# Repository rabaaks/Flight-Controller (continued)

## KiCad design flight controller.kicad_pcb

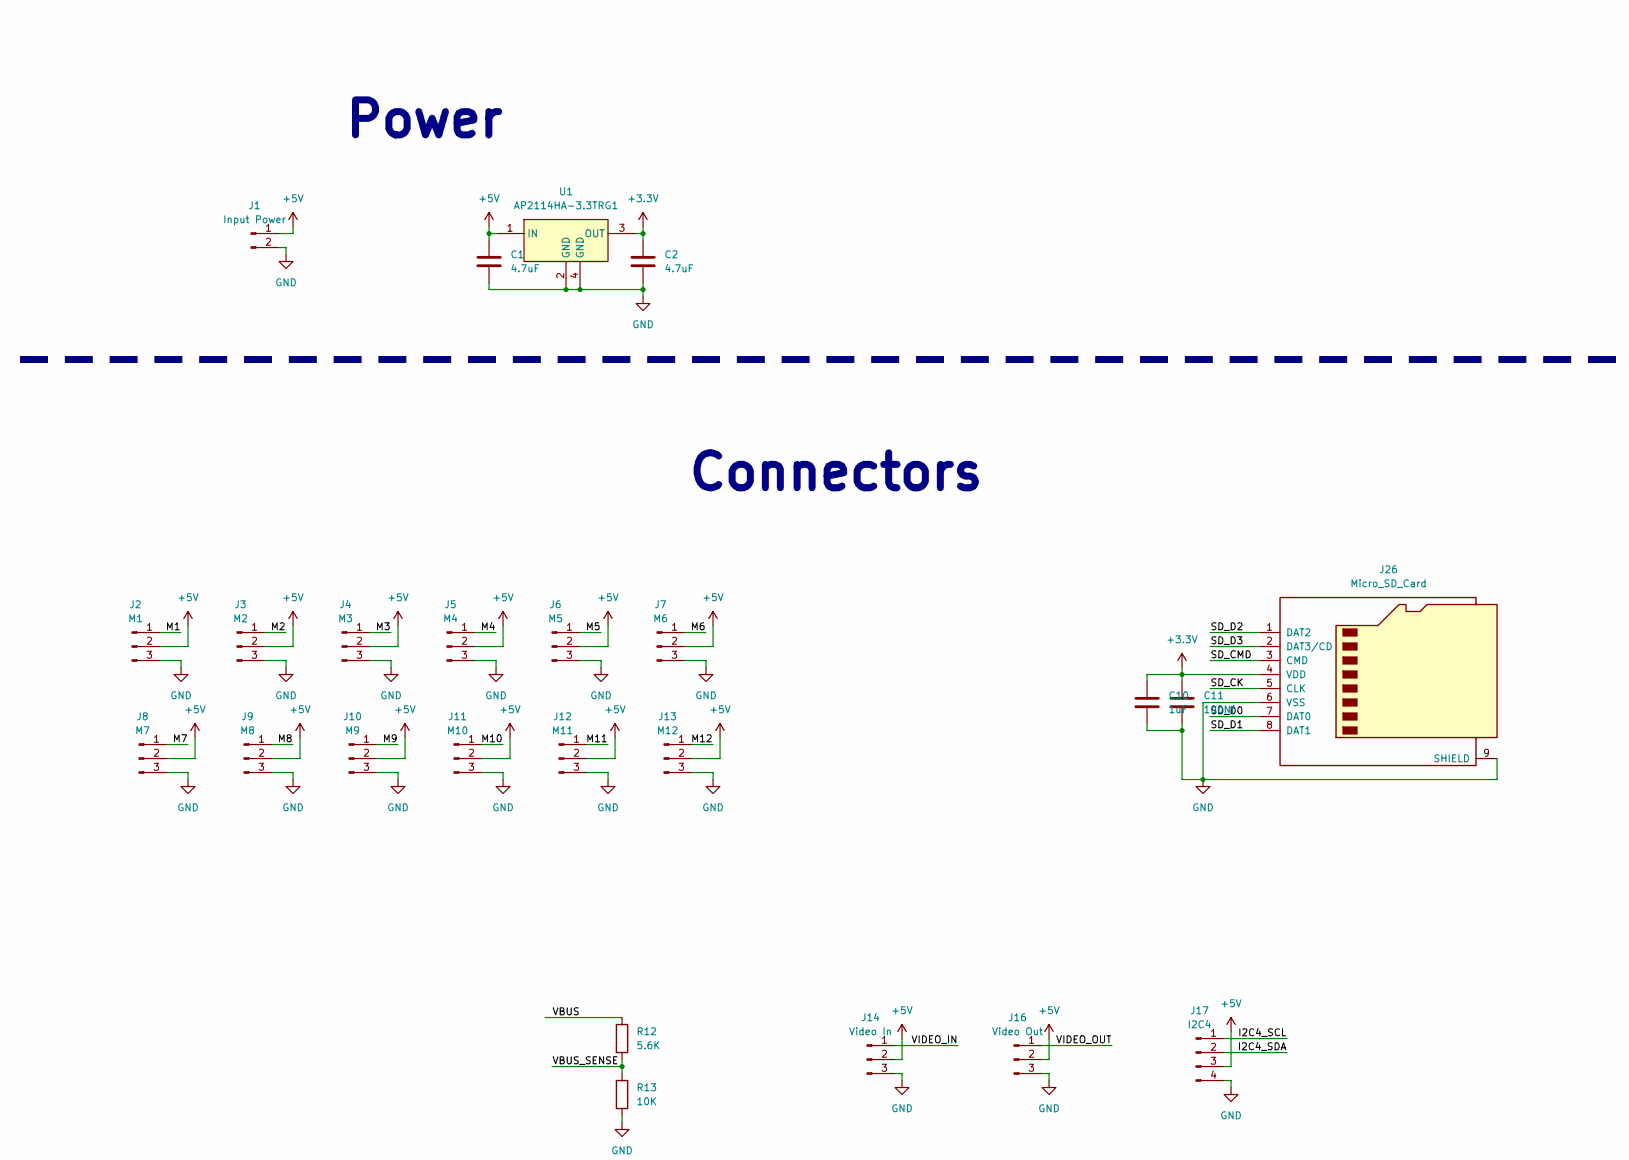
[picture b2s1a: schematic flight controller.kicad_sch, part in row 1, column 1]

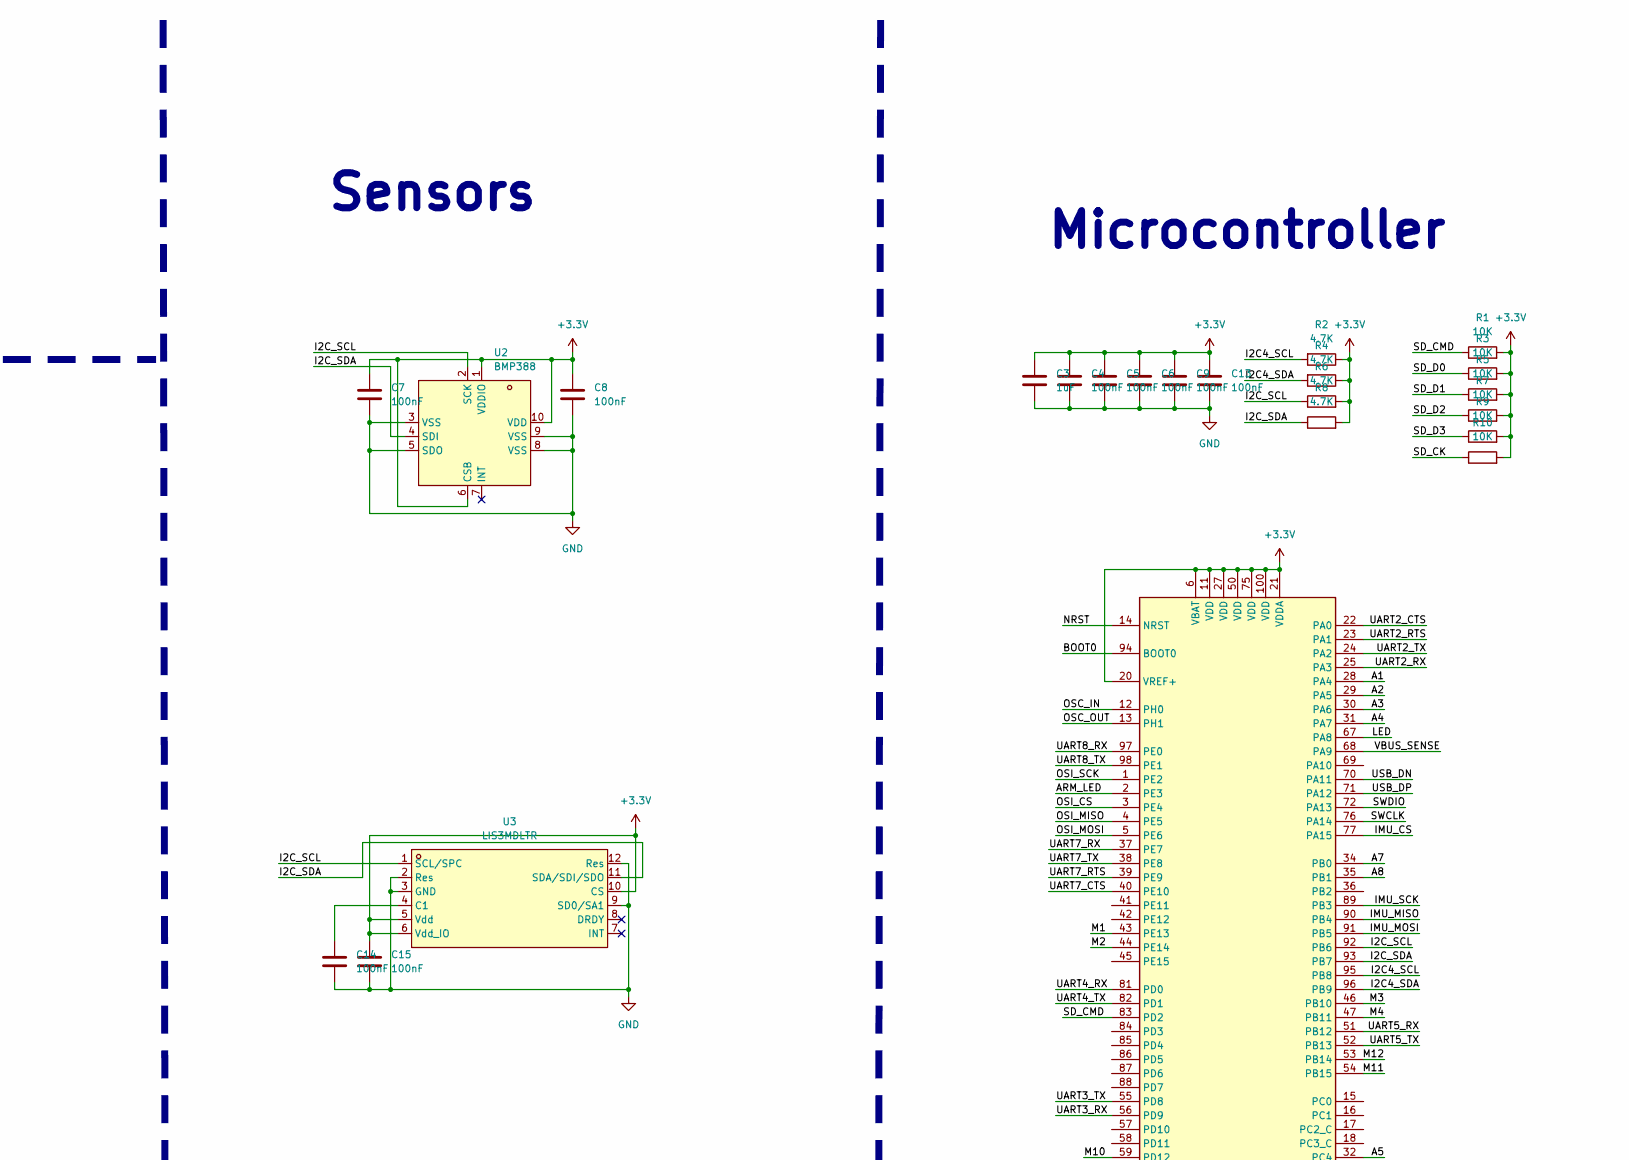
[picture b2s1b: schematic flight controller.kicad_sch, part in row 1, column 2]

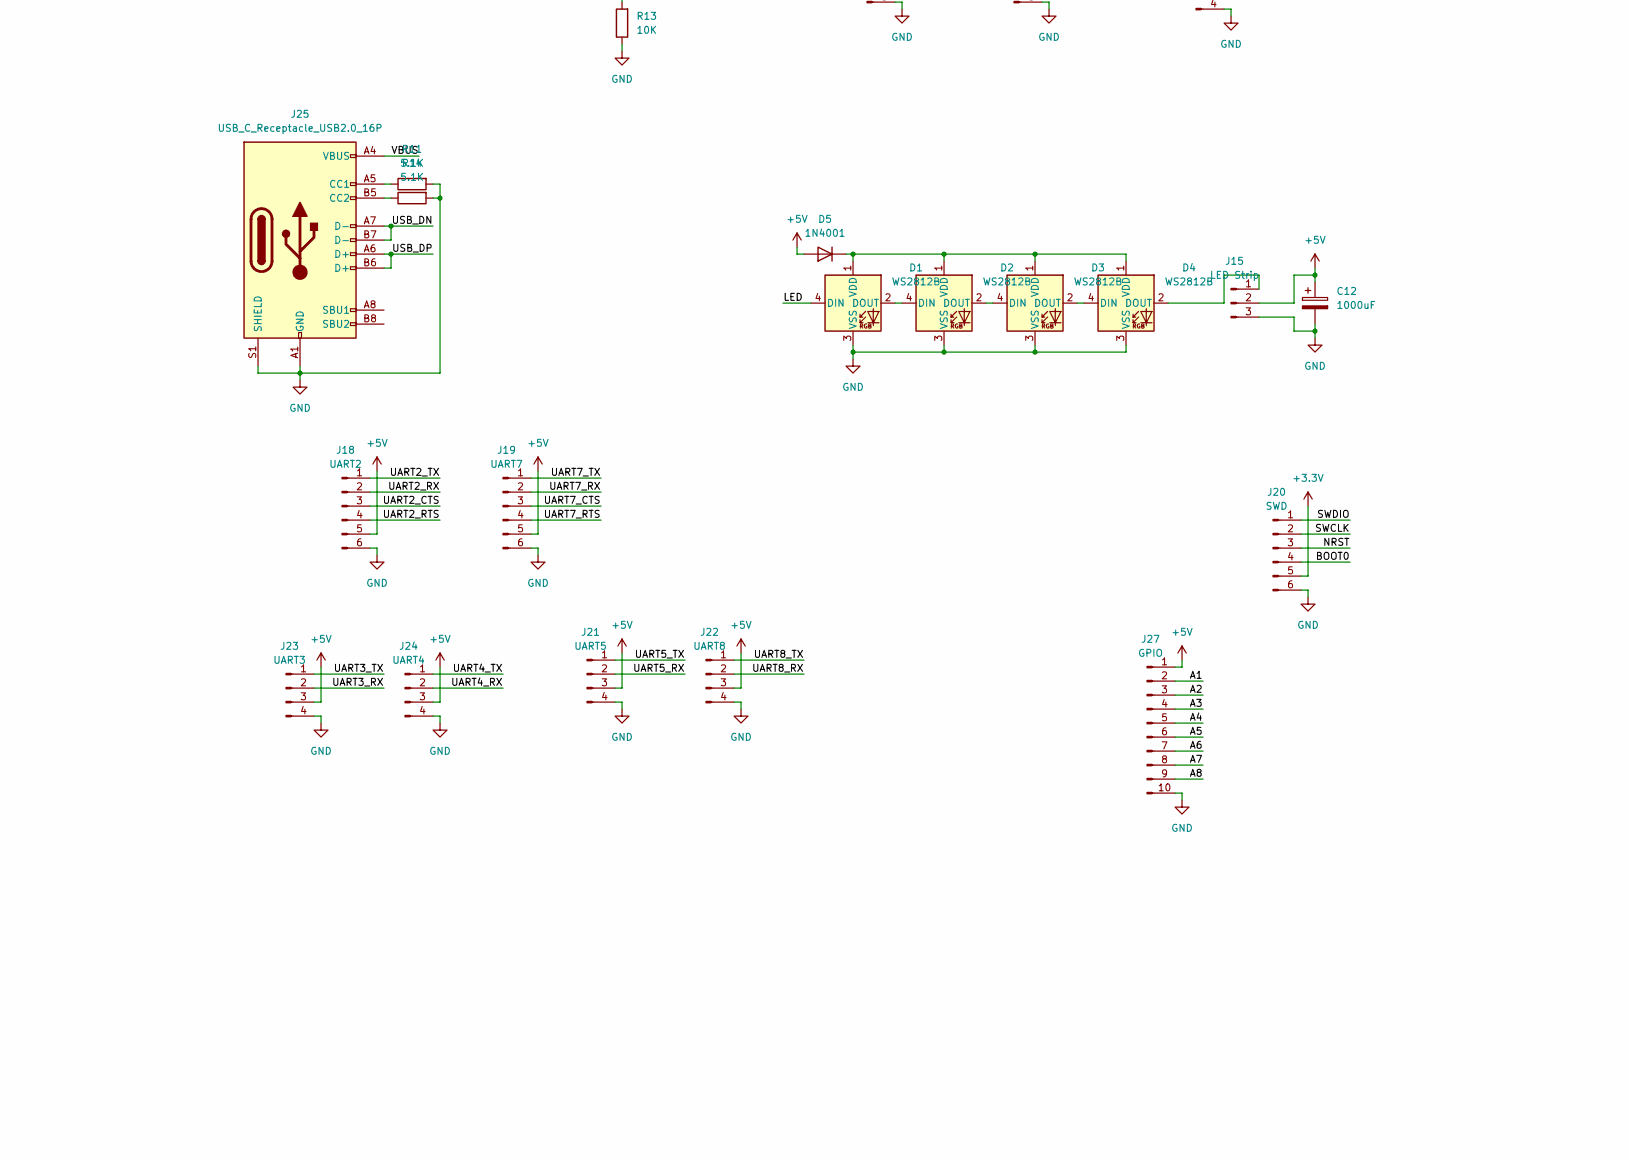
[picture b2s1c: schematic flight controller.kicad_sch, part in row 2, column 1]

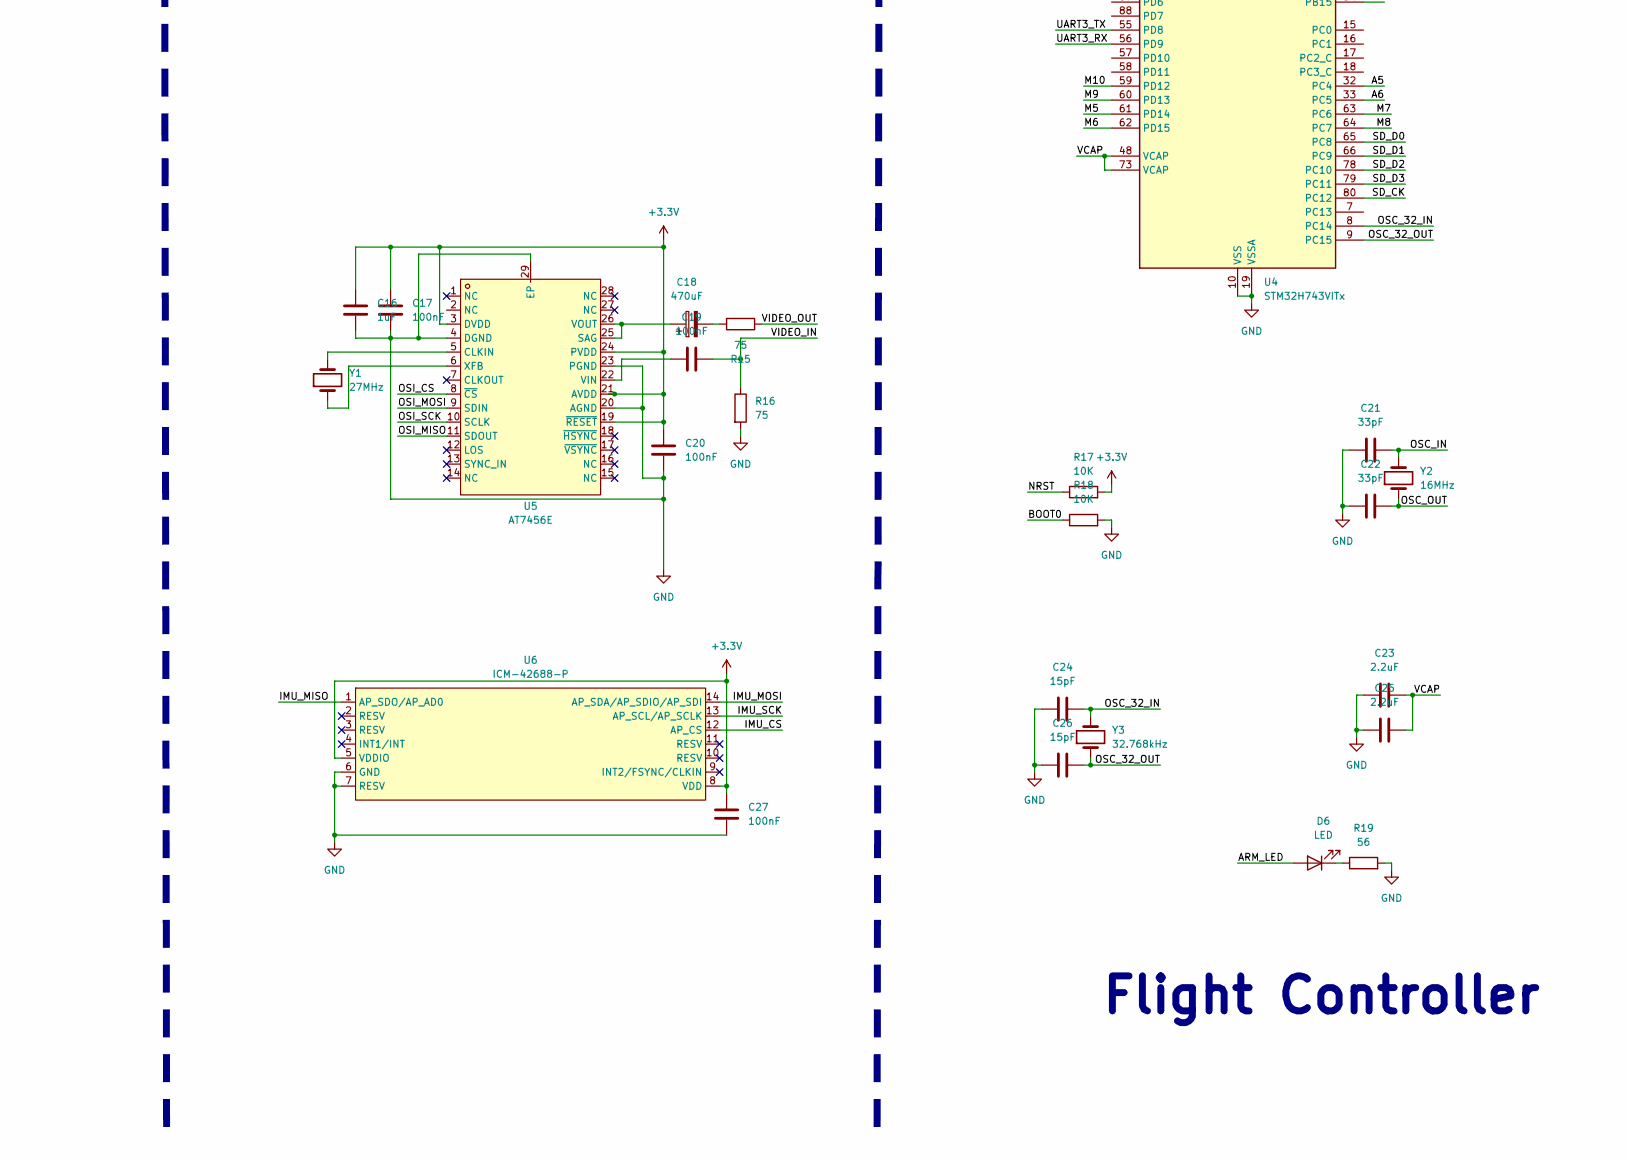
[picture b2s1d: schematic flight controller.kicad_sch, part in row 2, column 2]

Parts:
C1, C2: 4.7uF; C_0805_2012Metric
C3, C10, C16: 1uF; C_0805_2012Metric
C4, C5, C6, C7, C8, C9, C13, C14, C15, C17, C19, C20, C27: 100nF; C_0805_2012Metric
C11: 100Nf; C_0805_2012Metric
C12: 1000uF; CP_Radial_D8.0mm_P3.50mm
C18: 470uF; CP_Radial_D8.0mm_P3.50mm
C21, C22: 33pF; C_0805_2012Metric
C23, C25: 2.2uF; C_0805_2012Metric
C24, C26: 15pF; C_0805_2012Metric
D1, D2, D3, D4: WS2812B; LED_WS2812B_PLCC4_5.0x5.0mm_P3.2mm
D5: 1N4001; D_DO-41_SOD81_P7.62mm_Horizontal
D6: LED; LED_0805_2012Metric
J1: Input Power; AMASS_XT30PW-M_1x02_P2.50mm_Horizontal
J2: M1; JST_XH_B3B-XH-A_1x03_P2.50mm_Vertical
J3: M2; JST_XH_B3B-XH-A_1x03_P2.50mm_Vertical
J4: M3; JST_XH_B3B-XH-A_1x03_P2.50mm_Vertical
J5: M4; JST_XH_B3B-XH-A_1x03_P2.50mm_Vertical
J6: M5; JST_XH_B3B-XH-A_1x03_P2.50mm_Vertical
J7: M6; JST_XH_B3B-XH-A_1x03_P2.50mm_Vertical
J8: M7; JST_XH_B3B-XH-A_1x03_P2.50mm_Vertical
J9: M8; JST_XH_B3B-XH-A_1x03_P2.50mm_Vertical
J10: M9; JST_XH_B3B-XH-A_1x03_P2.50mm_Vertical
J11: M10; JST_XH_B3B-XH-A_1x03_P2.50mm_Vertical
J12: M11; JST_XH_B3B-XH-A_1x03_P2.50mm_Vertical
J13: M12; JST_XH_B3B-XH-A_1x03_P2.50mm_Vertical
J14: Video In; JST_XH_B3B-XH-A_1x03_P2.50mm_Vertical
J15: LED Strip; JST_XH_B3B-XH-A_1x03_P2.50mm_Vertical
J16: Video Out; JST_XH_B3B-XH-A_1x03_P2.50mm_Vertical
J17: I2C4; JST_XH_B4B-XH-A_1x04_P2.50mm_Vertical
J18: UART2; JST_XH_B6B-XH-A_1x06_P2.50mm_Vertical
J19: UART7; JST_XH_B6B-XH-A_1x06_P2.50mm_Vertical
J20: SWD; JST_XH_B6B-XH-A_1x06_P2.50mm_Vertical
J21: UART5; JST_XH_B4B-XH-A_1x04_P2.50mm_Vertical
J22: UART8; JST_XH_B4B-XH-A_1x04_P2.50mm_Vertical
J23: UART3; JST_XH_B4B-XH-A_1x04_P2.50mm_Vertical
J24: UART4; JST_XH_B4B-XH-A_1x04_P2.50mm_Vertical
J25: USB_C_Receptacle_USB2.0_16P; USB_C_Receptacle_HCTL_HC-TYPE-C-16P-01A
J26: Micro_SD_Card; TF-SMD_TF-PUSH
J27: GPIO; JST_XH_B10B-XH-A_1x10_P2.50mm_Vertical
R1, R3, R5, R7, R9, R10, R13, R17, R18: 10K; R_0805_2012Metric
R2, R4, R6, R8: 4.7K; R_0805_2012Metric
R11, R14: 5.1K; R_0805_2012Metric
R12: 5.6K; R_0805_2012Metric
R15, R16: 75; R_0805_2012Metric
R19: 56; R_0805_2012Metric
U1: AP2114HA-3.3TRG1; SOT-223; LCSC Part C460314
U2: BMP388; ST_HLGA-10_2x2mm_P0.5mm_LayoutBorder3x2y; LCSC Part C779278
U3: LIS3MDLTR; LGA-12_2x2mm_P0.5mm; LCSC Part C478483
U4: STM32H743VITx; LQFP-100_14x14mm_P0.5mm
U5: AT7456E; TSSOP-28-1EP_4.4x9.7mm_P0.65mm_EP2.85x6.7mm; LCSC Part C82351
U6: ICM-42688-P; LGA-14_3x2.5mm_P0.5mm_LayoutBorder3x4y; LCSC Part C1850418
Y1: 27MHz; Crystal_HC49-U_Vertical
Y2: 16MHz; Crystal_HC49-U_Vertical
Y3: 32.768kHz; Crystal_DS26_D2.0mm_L6.0mm_Horizontal

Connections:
+3.3V: C2.1, C3.2, C4.1, C5.2, C6.1, C7.1, C8.2, C9.2, C10.2, C11.2, C13.2, C15.1, C16.1, C17.1, C20.1, C27.2, J20.5, J26.4 (VDD), R1.2, R2.1, R3.2, R4.1, R5.2, R6.2, R7.2, R8.2, R9.2, R10.2, R17.2, U1.3 (OUT), U2.1 (VDDIO), U2.6 (CSB), U2.10 (VDD), U3.5 (Vdd), U3.6 (Vdd_IO), U3.10 (CS), U4.6 (VBAT), U4.11 (VDD), U4.20 (VREF+), U4.21 (VDDA), U4.27 (VDD), U4.50 (VDD), U4.75 (VDD), U4.100 (VDD), U5.3 (DVDD), U5.19 (~RESET), U5.21 (AVDD), U5.24 (PVDD), U6.5 (VDDIO), U6.8 (VDD)
+5V: C1.1, C12.1, D5.2 (A), J1.1, J2.2, J3.2, J4.2, J5.2, J6.2, J7.2, J8.2, J9.2, J10.2, J11.2, J12.2, J13.2, J14.2, J15.2, J16.2, J17.3, J18.5, J19.5, J21.3, J22.3, J23.3, J24.3, J27.1, U1.1 (IN)
/A1: J27.2, U4.28 (PA4)
/A2: J27.3, U4.29 (PA5)
/A3: J27.4, U4.30 (PA6)
/A4: J27.5, U4.31 (PA7)
/A5: J27.6, U4.32 (PC4)
/A6: J27.7, U4.33 (PC5)
/A7: J27.8, U4.34 (PB0)
/A8: J27.9, U4.35 (PB1)
/ARM_LED: D6.2 (A), U4.2 (PE3)
/BOOT0: J20.4, R18.1, U4.94 (BOOT0)
/I2C4_SCL: J17.1, R2.2, U4.95 (PB8)
/I2C4_SDA: J17.2, R4.2, U4.96 (PB9)
/I2C_SCL: R6.1, U2.2 (SCK), U3.1 (SCL/SPC), U4.92 (PB6)
/I2C_SDA: R8.1, U2.4 (SDI), U3.11 (SDA/SDI/SDO), U4.93 (PB7)
/IMU_CS: U4.77 (PA15), U6.12 (AP_CS)
/IMU_MISO: U4.90 (PB4), U6.1 (AP_SDO/AP_AD0)
/IMU_MOSI: U4.91 (PB5), U6.14 (AP_SDA/AP_SDIO/AP_SDI)
/IMU_SCK: U4.89 (PB3), U6.13 (AP_SCL/AP_SCLK)
/LED: D1.4 (DIN), U4.67 (PA8)
/M1: J2.1, U4.43 (PE13)
/M2: J3.1, U4.44 (PE14)
/M3: J4.1, U4.46 (PB10)
/M4: J5.1, U4.47 (PB11)
/M5: J6.1, U4.61 (PD14)
/M6: J7.1, U4.62 (PD15)
/M7: J8.1, U4.63 (PC6)
/M8: J9.1, U4.64 (PC7)
/M9: J10.1, U4.60 (PD13)
/M10: J11.1, U4.59 (PD12)
/M11: J12.1, U4.54 (PB15)
/M12: J13.1, U4.53 (PB14)
/NRST: J20.3, R17.1, U4.14 (NRST)
/OSC_32_IN: C24.1, U4.8 (PC14), Y3.2
/OSC_32_OUT: C26.2, U4.9 (PC15), Y3.1
/OSC_IN: C21.1, U4.12 (PH0), Y2.2
/OSC_OUT: C22.2, U4.13 (PH1), Y2.1
/OSI_CS: U4.3 (PE4), U5.8 (~CS)
/OSI_MISO: U4.4 (PE5), U5.11 (SDOUT)
/OSI_MOSI: U4.5 (PE6), U5.9 (SDIN)
/OSI_SCK: U4.1 (PE2), U5.10 (SCLK)
/SD_CK: J26.5 (CLK), R10.1, U4.80 (PC12)
/SD_CMD: J26.3 (CMD), R1.1, U4.83 (PD2)
/SD_D0: J26.7 (DAT0), R3.1, U4.65 (PC8)
/SD_D1: J26.8 (DAT1), R5.1, U4.66 (PC9)
/SD_D2: J26.1 (DAT2), R7.1, U4.78 (PC10)
/SD_D3: J26.2 (DAT3/CD), R9.1, U4.79 (PC11)
/SWCLK: J20.2, U4.76 (PA14)
/SWDIO: J20.1, U4.72 (PA13)
/UART2_CTS: J18.3, U4.22 (PA0)
/UART2_RTS: J18.4, U4.23 (PA1)
/UART2_RX: J18.2, U4.25 (PA3)
/UART2_TX: J18.1, U4.24 (PA2)
/UART3_RX: J23.2, U4.56 (PD9)
/UART3_TX: J23.1, U4.55 (PD8)
/UART4_RX: J24.2, U4.81 (PD0)
/UART4_TX: J24.1, U4.82 (PD1)
/UART5_RX: J21.2, U4.51 (PB12)
/UART5_TX: J21.1, U4.52 (PB13)
/UART7_CTS: J19.3, U4.40 (PE10)
/UART7_RTS: J19.4, U4.39 (PE9)
/UART7_RX: J19.2, U4.37 (PE7)
/UART7_TX: J19.1, U4.38 (PE8)
/UART8_RX: J22.2, U4.97 (PE0)
/UART8_TX: J22.1, U4.98 (PE1)
/USB_DN: J25.A7 (D-), J25.B7 (D-), U4.70 (PA11)
/USB_DP: J25.A6 (D+), J25.B6 (D+), U4.71 (PA12)
/VBUS: J25.A4 (VBUS), J25.A9 (VBUS), J25.B4 (VBUS), J25.B9 (VBUS), R12.1
/VBUS_SENSE: R12.2, R13.2, U4.68 (PA9)
/VCAP: C23.1, C25.1, U4.48 (VCAP), U4.73 (VCAP)
/VIDEO_IN: C19.2, J14.1, R16.1
/VIDEO_OUT: J16.1, R15.1
GND: C1.2, C2.2, C3.1, C4.2, C5.1, C6.2, C7.2, C8.1, C9.1, C10.1, C11.1, C12.2, C13.1, C14.2, C15.2, C16.2, C17.2, C20.2, C21.2, C22.1, C23.2, C24.2, C25.2, C26.1, C27.1, D1.3 (VSS), D2.3 (VSS), D3.3 (VSS), D4.3 (VSS), J1.2, J2.3, J3.3, J4.3, J5.3, J6.3, J7.3, J8.3, J9.3, J10.3, J11.3, J12.3, J13.3, J14.3, J15.3, J16.3, J17.4, J18.6, J19.6, J20.6, J21.4, J22.4, J23.4, J24.4, J25.A1 (GND), J25.A12 (GND), J25.B1 (GND), J25.B12 (GND), J25.S1 (SHIELD), J26.6 (VSS), J26.9 (SHIELD), J27.10, R11.2, R13.1, R14.2, R16.2, R18.2, R19.2, U1.2 (GND), U1.4 (GND), U2.3 (VSS), U2.5 (SDO), U2.8 (VSS), U2.9 (VSS), U3.2 (Res), U3.3 (GND), U3.9 (SD0/SA1), U3.12 (Res), U4.10 (VSS), U4.19 (VSSA), U4.26 (VSS), U4.49 (VSS), U4.74 (VSS), U4.99 (VSS), U5.4 (DGND), U5.20 (AGND), U5.23 (PGND), U5.29 (EP), U6.6 (GND), U6.7 (RESV)
unnamed: C18.2, R15.2
unnamed: D1.2 (DOUT), D2.4 (DIN)
unnamed: D1.1 (VDD), D2.1 (VDD), D3.1 (VDD), D4.1 (VDD), D5.1 (K)
unnamed: D2.2 (DOUT), D3.4 (DIN)
unnamed: D3.2 (DOUT), D4.4 (DIN)
unnamed: D4.2 (DOUT), J15.1
unnamed: D6.1 (K), R19.1
unnamed: J25.A5 (CC1), R11.1
unnamed: J25.B5 (CC2), R14.1
unnamed: C14.1, U3.4 (C1)
unnamed: U5.5 (CLKIN), Y1.2
unnamed: C18.1, U5.25 (SAG), U5.26 (VOUT)
unnamed: C19.1, U5.22 (VIN)
unnamed: U5.6 (XFB), Y1.1

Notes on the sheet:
Microcontroller
Connectors
Sensors
Flight Controller
Power

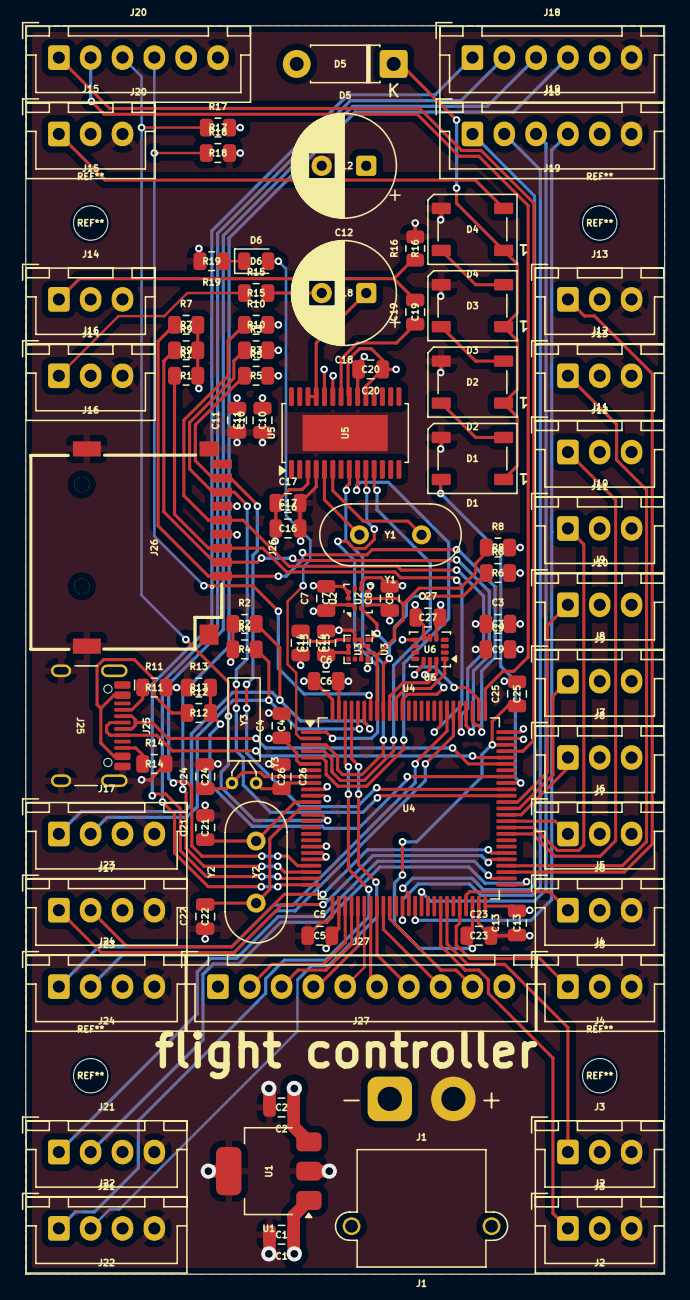
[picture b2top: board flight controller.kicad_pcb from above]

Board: 4 copper layers, 50.2 x 98.1 mm, 88 parts (0 on the bottom side), 88 nets.

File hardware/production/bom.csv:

Designator,Footprint,Quantity,Value,LCSC Part #
"C1, C2",0805,2,4.7uF,
"C10, C16, C3",0805,3,1uF,
"C11, C13, C14, C15, C17, C19, C20, C27, C4, C5, C6, C7, C8, C9",0805,14,100Nf,
C12,CP_Radial_D8.0mm_P3.50mm,1,1000uF,
C18,CP_Radial_D8.0mm_P3.50mm,1,470uF,
"C21, C22",0805,2,33pF,
"C23, C25",0805,2,2.2uF,
"C24, C26",0805,2,15pF,
"D1, D2, D3, D4",LED_WS2812B_PLCC4_5.0x5.0mm_P3.2mm,4,WS2812B,
D5,D_DO-41_SOD81_P7.62mm_Horizontal,1,1N4001,
D6,0805,1,LED,
J1,AMASS_XT30PW-M_1x02_P2.50mm_Horizontal,1,Input Power,
J10,JST_XH_B3B-XH-A_1x03_P2.50mm_Vertical,1,M9,
J11,JST_XH_B3B-XH-A_1x03_P2.50mm_Vertical,1,M10,
J12,JST_XH_B3B-XH-A_1x03_P2.50mm_Vertical,1,M11,
J13,JST_XH_B3B-XH-A_1x03_P2.50mm_Vertical,1,M12,
J14,JST_XH_B3B-XH-A_1x03_P2.50mm_Vertical,1,Video In,
J15,JST_XH_B3B-XH-A_1x03_P2.50mm_Vertical,1,LED Strip,
J16,JST_XH_B3B-XH-A_1x03_P2.50mm_Vertical,1,Video Out,
J17,JST_XH_B4B-XH-A_1x04_P2.50mm_Vertical,1,I2C4,
J18,JST_XH_B6B-XH-A_1x06_P2.50mm_Vertical,1,UART2,
J19,JST_XH_B6B-XH-A_1x06_P2.50mm_Vertical,1,UART7,
J2,JST_XH_B3B-XH-A_1x03_P2.50mm_Vertical,1,M1,
J20,JST_XH_B6B-XH-A_1x06_P2.50mm_Vertical,1,SWD,
J21,JST_XH_B4B-XH-A_1x04_P2.50mm_Vertical,1,UART5,
J22,JST_XH_B4B-XH-A_1x04_P2.50mm_Vertical,1,UART8,
J23,JST_XH_B4B-XH-A_1x04_P2.50mm_Vertical,1,UART3,
J24,JST_XH_B4B-XH-A_1x04_P2.50mm_Vertical,1,UART4,
J25,USB_C_Receptacle_HCTL_HC-TYPE-C-16P-01A,1,USB_C_Receptacle_USB2.0_16P,
J26,TF-SMD_TF-PUSH,1,Micro_SD_Card,
J27,JST_XH_B10B-XH-A_1x10_P2.50mm_Vertical,1,GPIO,
J3,JST_XH_B3B-XH-A_1x03_P2.50mm_Vertical,1,M2,
J4,JST_XH_B3B-XH-A_1x03_P2.50mm_Vertical,1,M3,
J5,JST_XH_B3B-XH-A_1x03_P2.50mm_Vertical,1,M4,
J6,JST_XH_B3B-XH-A_1x03_P2.50mm_Vertical,1,M5,
J7,JST_XH_B3B-XH-A_1x03_P2.50mm_Vertical,1,M6,
J8,JST_XH_B3B-XH-A_1x03_P2.50mm_Vertical,1,M7,
J9,JST_XH_B3B-XH-A_1x03_P2.50mm_Vertical,1,M8,
"R1, R10, R13, R17, R18, R3, R5, R7, R9",0805,9,10K,
"R11, R14",0805,2,5.1K,
R12,0805,1,5.6K,
"R15, R16",0805,2,75,
R19,0805,1,56,
"R2, R4, R6, R8",0805,4,4.7K,
U1,SOT-223,1,AP2114HA-3.3TRG1,C460314
U2,ST_HLGA-10_2x2mm_P0.5mm_LayoutBorder3x2y,1,BMP388,C779278
U3,LGA-12_2x2mm_P0.5mm,1,LIS3MDLTR,C478483
U4,LQFP-100_14x14mm_P0.5mm,1,STM32H743VITx,
U5,TSSOP-28-1EP_4.4x9.7mm_P0.65mm_EP2.85x6.7mm,1,AT7456E,C82351
U6,LGA-14_3x2.5mm_P0.5mm_LayoutBorder3x4y,1,ICM-42688-P,C1850418
Y1,Crystal_HC49-U_Vertical,1,27MHz,
Y2,Crystal_HC49-U_Vertical,1,16MHz,
Y3,Crystal_DS26_D2.0mm_L6.0mm_Horizontal,1,32.768kHz,

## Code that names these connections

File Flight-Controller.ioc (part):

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Mcu.Name=STM32H743VITx
Mcu.Package=LQFP100
Mcu.UserName=STM32H743VITx
PA0.Signal=S_TIM5_CH1
PA1.Signal=S_TIM5_CH2
PA11.Mode=Device_Only
PA11.Signal=USB_OTG_FS_DM
PA12.Mode=Device_Only
PA12.Signal=USB_OTG_FS_DP
PA13\ (JTMS/SWDIO).Mode=Serial_Wire
PA13\ (JTMS/SWDIO).Signal=DEBUG_JTMS-SWDIO
PA14\ (JTCK/SWCLK).Mode=Serial_Wire
PA14\ (JTCK/SWCLK).Signal=DEBUG_JTCK-SWCLK
PA15\ (JTDI).Mode=NSS_Signal_Hard_Output
PA15\ (JTDI).Signal=SPI1_NSS
PA2.Signal=S_TIM5_CH3
PA3.Signal=S_TIM5_CH4
PA4.Signal=ADCx_INP18
PA5.Signal=ADCx_INP19
PA6.Signal=ADCx_INP3
PA7.Signal=ADCx_INP7
PA9.Mode=Activate_VBUS
PA9.Signal=USB_OTG_FS_VBUS
PB0.Signal=ADCx_INP9
PB1.Signal=ADCx_INP5
PB10.Signal=S_TIM2_CH3
PB11.Signal=S_TIM2_CH4
PB12.Mode=Asynchronous
PB12.Signal=UART5_RX
PB13.Mode=Asynchronous
PB13.Signal=UART5_TX
PB14.Signal=S_TIM12_CH1
PB15.Signal=S_TIM12_CH2
PB3\ (JTDO/TRACESWO).Mode=Full_Duplex_Master
PB3\ (JTDO/TRACESWO).Signal=SPI1_SCK
PB4\ (NJTRST).Mode=Full_Duplex_Master
PB4\ (NJTRST).Signal=SPI1_MISO
PB5.Mode=Full_Duplex_Master
PB5.Signal=SPI1_MOSI
PB6.Mode=I2C
PB6.Signal=I2C1_SCL
PB7.Mode=I2C
PB7.Signal=I2C1_SDA
PB8.Mode=I2C
PB8.Signal=I2C4_SCL
PB9.Mode=I2C
PB9.Signal=I2C4_SDA
PC10.Mode=SD_4_bits_Wide_bus
PC10.Signal=SDMMC1_D2
PC11.Mode=SD_4_bits_Wide_bus
PC11.Signal=SDMMC1_D3
PC12.Mode=SD_4_bits_Wide_bus
PC12.Signal=SDMMC1_CK
PC13.Signal=GPIO_Output
PC14-OSC32_IN\ (OSC32_IN).Mode=LSE-External-Oscillator
PC14-OSC32_IN\ (OSC32_IN).Signal=RCC_OSC32_IN
PC15-OSC32_OUT\ (OSC32_OUT).Mode=LSE-External-Oscillator
PC15-OSC32_OUT\ (OSC32_OUT).Signal=RCC_OSC32_OUT
PC4.Signal=ADCx_INP4
PC5.Signal=ADCx_INP8
PC6.Mode=Asynchronous
PC6.Signal=USART6_TX
PC7.Mode=Asynchronous
PC7.Signal=USART6_RX
PC8.Mode=SD_4_bits_Wide_bus
PC8.Signal=SDMMC1_D0
PC9.Mode=SD_4_bits_Wide_bus
PC9.Signal=SDMMC1_D1
PD0.Mode=Asynchronous
PD0.Signal=UART4_RX
PD1.Mode=Asynchronous
PD1.Signal=UART4_TX
PD11.Mode=CTS_RTS
PD11.Signal=USART3_CTS
PD12.Mode=CTS_RTS
PD12.Signal=USART3_RTS
PD2.Mode=SD_4_bits_Wide_bus
PD2.Signal=SDMMC1_CMD
PD3.Mode=CTS_RTS
PD3.Signal=USART2_CTS
PD4.Mode=CTS_RTS
PD4.Signal=USART2_RTS
PD5.Mode=Asynchronous
PD5.Signal=USART2_TX
PD6.Mode=Asynchronous
PD6.Signal=USART2_RX
PD8.Mode=Asynchronous
PD8.Signal=USART3_TX
PD9.Mode=Asynchronous
PD9.Signal=USART3_RX
PE0.Mode=Asynchronous
PE0.Signal=UART8_RX
PE1.Mode=Asynchronous
PE1.Signal=UART8_TX
PE11.Signal=S_TIM1_CH2
PE13.Signal=S_TIM1_CH3
PE14.Signal=S_TIM1_CH4
PE2.Mode=Full_Duplex_Master
PE2.Signal=SPI4_SCK
PE4.Mode=NSS_Signal_Hard_Output
PE4.Signal=SPI4_NSS
PE5.Mode=Full_Duplex_Master
PE5.Signal=SPI4_MISO
PE6.Mode=Full_Duplex_Master
PE6.Signal=SPI4_MOSI
PE9.Signal=S_TIM1_CH1
PH0-OSC_IN\ (PH0).Mode=HSE-External-Oscillator
PH0-OSC_IN\ (PH0).Signal=RCC_OSC_IN
PH1-OSC_OUT\ (PH1).Mode=HSE-External-Oscillator
PH1-OSC_OUT\ (PH1).Signal=RCC_OSC_OUT
RCC.HSE_VALUE=16000000
RCC.SYSCLKFreq_VALUE=480000000
RCC.SYSCLKSource=RCC_SYSCLKSOURCE_PLLCLK
board=custom

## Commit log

2025-12-28 init
2026-01-18 finished pcb
2026-01-18 add images and readme
2026-01-18 ardupilot hwdef files
2026-01-19 finished bom
2026-01-19 remove production folder
2026-01-19 space
2026-01-19 changed the regulator to a buck converter
2026-01-19 added antenna stuff
2026-01-19 update bom
2026-01-19 update images
2026-01-19 update redame
2026-01-22 smd crystal
2026-01-22 smol
2026-01-23 some routing
2026-01-23 more routing
2026-01-29 finish v2
2026-01-30 test
2026-01-31 add gerber files
2026-01-31 update bom, fix some clearance issue
